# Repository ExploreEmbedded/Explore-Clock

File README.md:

# FunTime
FunTime is a simple DIY clock kit, that doubles up as automatic night lamp. While building this kit we learn about how time is computed, converted to secs, mins, hours, days and eventually into years! We will also learn about measuring light and controlling a LED depending on time and light. The end goal is build a cool wall clock, use the time and the light intensity to turn on the night lamp. It will take about an hour to solder and assemble the kit.

Get one at:
https://www.exploreembedded.com/product/funTime 

Acrylic Design

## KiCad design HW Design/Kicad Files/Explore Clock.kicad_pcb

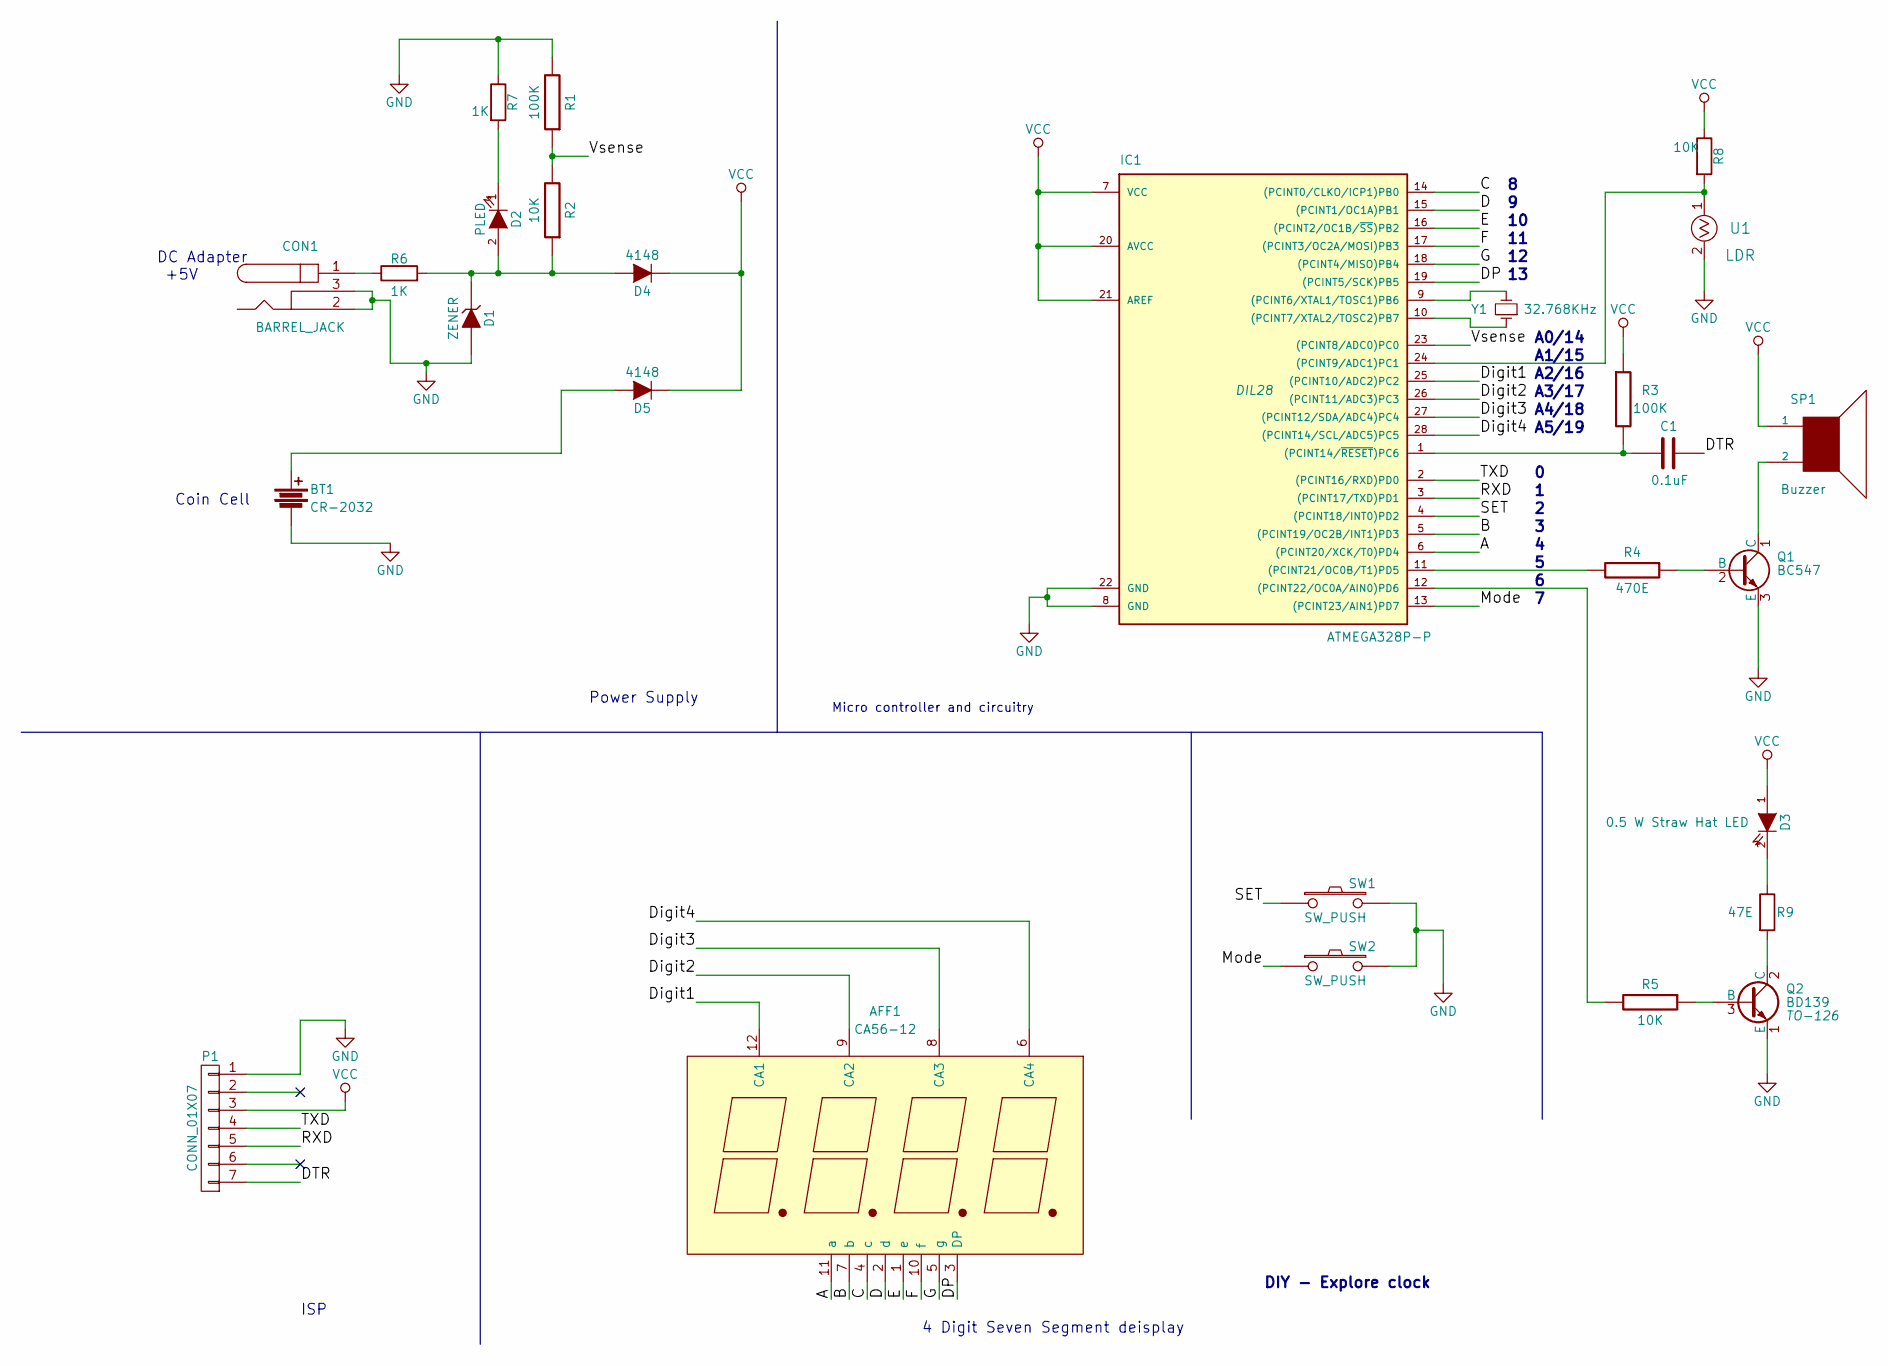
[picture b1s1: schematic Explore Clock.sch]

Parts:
AFF1: CA56-12
BT1: CR-2032
C1: 0.1uF
CON1: BARREL_JACK
D1: ZENER
D2: PLED
D3: 0.5 W Straw Hat LED
D4, D5: 4148
IC1: ATMEGA328P-P; DIL28
P1: CONN_01X07
Q1: BC547; TO-92
Q2: BD139; TO-126
R1, R3: 100K
R2, R5, R8: 10K
R4: 470E
R6, R7: 1K
R9: 47E
SP1: Buzzer
SW1, SW2: SW_PUSH
U1: LDR
Y1: 32.768KHz

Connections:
/A: AFF1.11 (a), IC1.6 ((PCINT20/XCK/T0)PD4)
/B: AFF1.7 (b), IC1.5 ((PCINT19/OC2B/INT1)PD3)
/C: AFF1.4 (c), IC1.14 ((PCINT0/CLKO/ICP1)PB0)
/D: AFF1.2 (d), IC1.15 ((PCINT1/OC1A)PB1)
/DP: AFF1.3 (DP), IC1.19 ((PCINT5/SCK)PB5)
/DTR: C1.1, P1.7
/Digit1: AFF1.12 (CA1), IC1.25 ((PCINT10/ADC2)PC2)
/Digit2: AFF1.9 (CA2), IC1.26 ((PCINT11/ADC3)PC3)
/Digit3: AFF1.8 (CA3), IC1.27 ((PCINT12/SDA/ADC4)PC4)
/Digit4: AFF1.6 (CA4), IC1.28 ((PCINT14/SCL/ADC5)PC5)
/E: AFF1.1 (e), IC1.16 ((PCINT2/OC1B/~SS~)PB2)
/F: AFF1.10 (f), IC1.17 ((PCINT3/OC2A/MOSI)PB3)
/G: AFF1.5 (g), IC1.18 ((PCINT4/MISO)PB4)
/Mode: IC1.13 ((PCINT23/AIN1)PD7), SW2.1
/RXD: IC1.3 ((PCINT17/TXD)PD1), P1.5
/SET: IC1.4 ((PCINT18/INT0)PD2), SW1.1
/TXD: IC1.2 ((PCINT16/RXD)PD0), P1.4
/Vsense: IC1.23 ((PCINT8/ADC0)PC0), R1.1, R2.2
GND: BT1.2, CON1.2, CON1.3, D1.2 (A), IC1.8 (GND), IC1.22 (GND), P1.1, Q1.3 (E), Q2.1 (E), R1.2, R7.1, SW1.2, SW2.2, U1.2
unnamed: BT1.1, D5.2 (A)
unnamed: C1.2, IC1.1 ((PCINT14/~RESET~)PC6), R3.2
unnamed: CON1.1, R6.1
unnamed: D1.1 (K), D2.2 (A), D4.2 (A), R2.1, R6.2
unnamed: D2.1 (K), R7.2
unnamed: D3.2 (K), R9.1
unnamed: IC1.9 ((PCINT6/XTAL1/TOSC1)PB6), Y1.2
unnamed: IC1.10 ((PCINT7/XTAL2/TOSC2)PB7), Y1.1
unnamed: IC1.11 ((PCINT21/OC0B/T1)PD5), R4.2
unnamed: IC1.12 ((PCINT22/OC0A/AIN0)PD6), R5.2
unnamed: IC1.24 ((PCINT9/ADC1)PC1), R8.2, U1.1
unnamed: Q1.1 (C), SP1.2
unnamed: Q1.2 (B), R4.1
unnamed: Q2.2 (C), R9.2
unnamed: Q2.3 (B), R5.1
VCC: D3.1 (A), D4.1 (K), D5.1 (K), IC1.7 (VCC), IC1.20 (AVCC), IC1.21 (AREF), P1.3, R3.1, R8.1, SP1.1

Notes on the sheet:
DIY - Explore clock
DC Adapter +5V
Coin Cell
Power Supply
ISP
4 Digit Seven Segment deisplay
Micro controller and circuitry
/14
/15
/16
/17
/18
/19

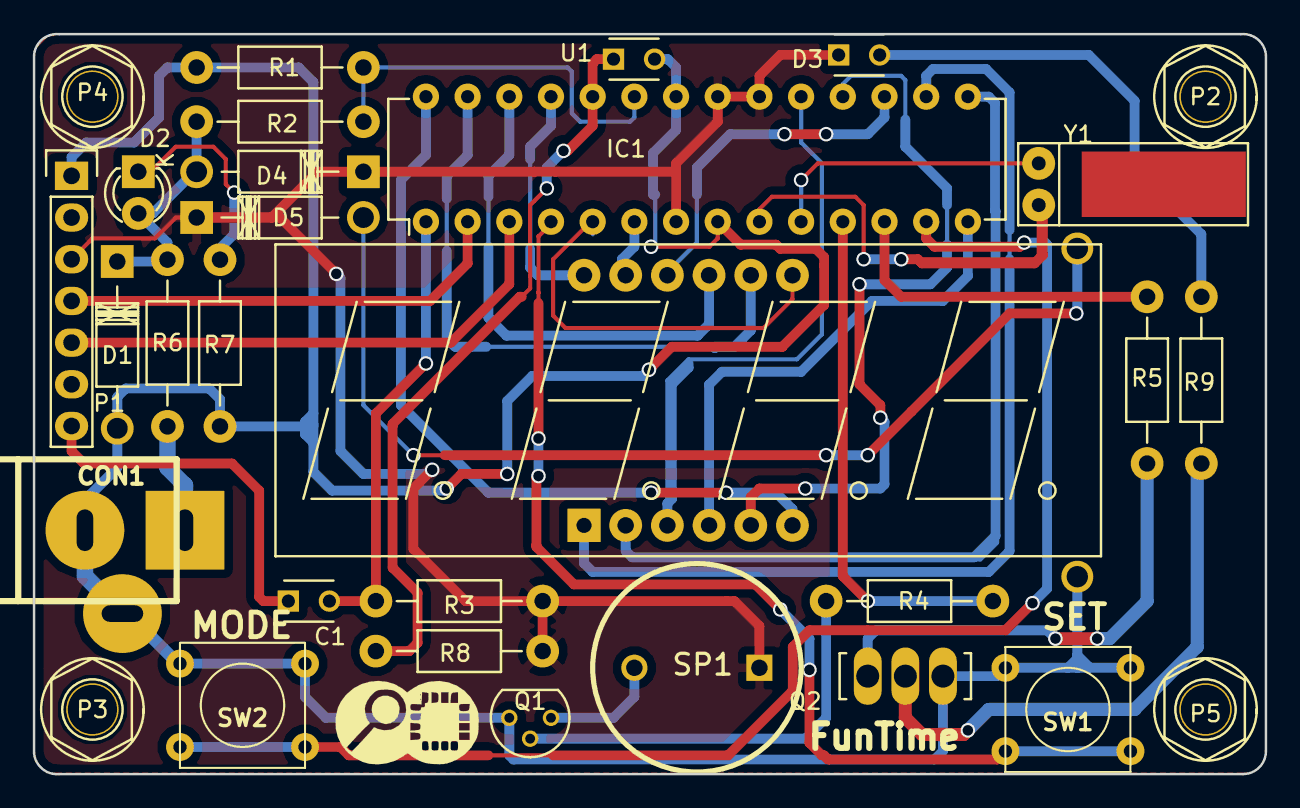
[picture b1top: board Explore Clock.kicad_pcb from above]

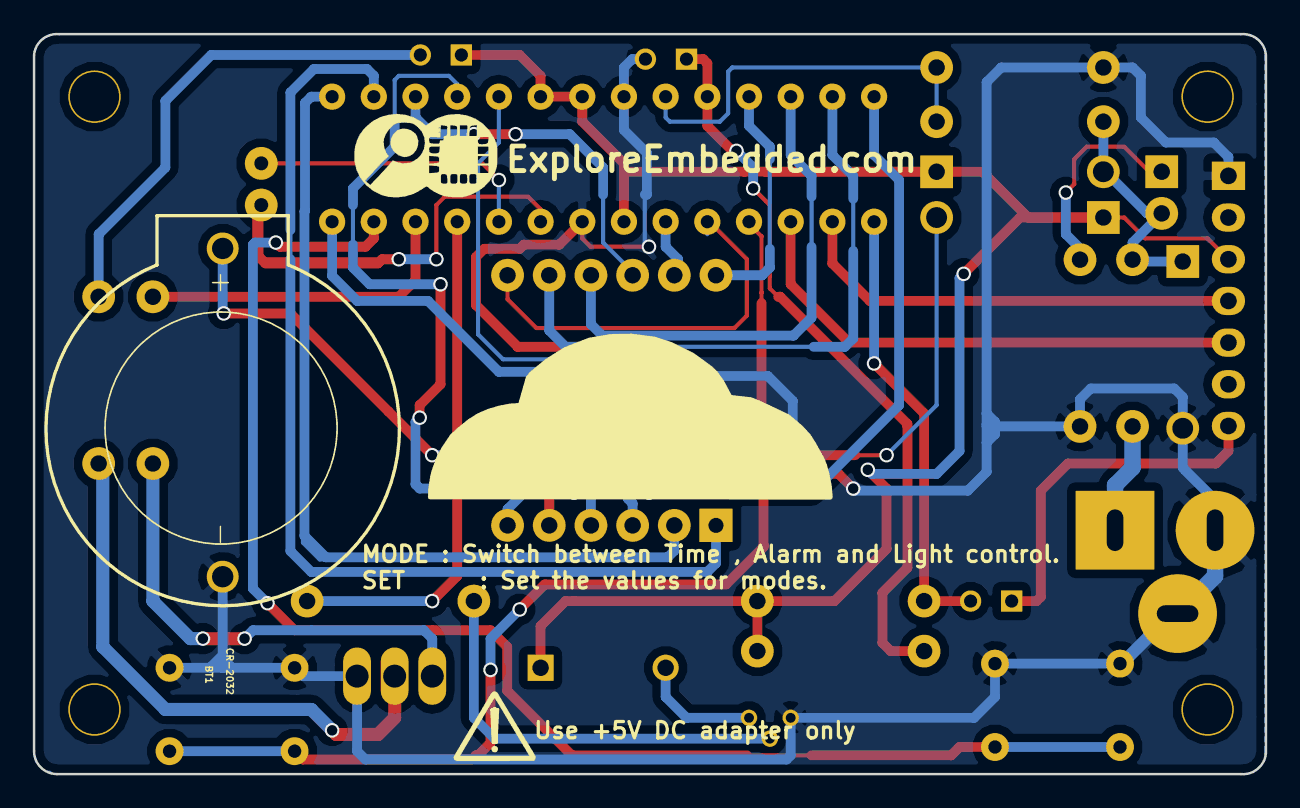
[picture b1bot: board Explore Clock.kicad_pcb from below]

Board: 2 copper layers, 75.1 x 45.1 mm, 33 parts (2 on the bottom side), 35 nets.

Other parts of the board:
P2, P3, P4, P5: CONN_01X01; M3_mounting
P14, P14#2: CONN_01X01; Logo_8

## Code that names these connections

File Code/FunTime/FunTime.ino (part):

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
//-=-=-=-=-=-=-=-=-=-=-=-=-=-=-=-=-=-=
//Pin definitions
int digit1 = A2; //Display pin 1
int digit2 = A3; //Display pin 2
int digit3 = A4; //Display pin 6
int digit4 = A5; //Display pin 8

int segA = 4; //Display pin 14
int segB = 3; //Display pin 16
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  pinMode(segF, OUTPUT);
  pinMode(segG, OUTPUT);

  pinMode(digit1, OUTPUT);
  pinMode(digit2, OUTPUT);
  pinMode(digit3, OUTPUT);
  pinMode(digit4, OUTPUT);
  pinMode(colons, OUTPUT);
  pinMode(ampm, OUTPUT);

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
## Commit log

2016-10-01 Schematic Update
2016-10-03 design idea for the case
2016-10-03 sketch to test power source
2016-10-04 Added LDR, Changed Vsense ciruit
2016-10-04 0.5W LED Driving circuit added
2016-10-06 Power LED added
2016-10-07 Layout For pcb and Acrylic Design Uploaded
2016-10-07 CorelDraw v0.1
2016-10-10 renamed imp directories, test code added
2016-10-11 added bootloader hex and fuse bits
2016-10-11 updated code to test watch
2016-10-11 Added hole for LDR in Acrylic case
2016-10-13 added zener diode , INT0 used for switch SET and BD139 for LED
2016-10-14 Kicad Design files ready for manufacturing
2016-11-22 auto turn on functionality
2016-11-30 Acrylic Enclosure design updated for 5mm sheet
2016-11-30 Assemly BOM Generated
